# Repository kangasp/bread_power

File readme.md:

# Bread Board Power Module
Goal is to power a bread board.

## Reqs
* Use 18650 to power the board
* Ability to charge the battery with USB-C
* Form factor for bread board
* LEDs to indicate on / charging
* Fuse - resetable circuit protection

## Parts to use
* Boost:  C915088 Boost IC, TPS61022RWUR
* BMS:  C15220, BQ24073RGTR,    https://www.ti.com/lit/ds/symlink/bq24073.pdf?ts=1761246632036&ref_url=https%253A%252F%252Fwww.ti.com%252Fproduct%252FBQ24073%252Fpart-details%252FBQ24073RGTR%253Futm_source%253Dgoogle%2526utm_medium%253Dcpc%2526utm_campaign%253Dapp-null-null-app_opn_en-cpc-storeic-google-ww_en_pur%2526utm_content%253DDevice%2526ds_k%253DBQ24073RGTR%2526DCM%253Dyes%2526gclsrc%253Daw.ds%2526gad_source%253D1%2526gad_campaignid%253D8178941673%2526gbraid%253D0AAAAAC068F1OY5LTfCSqCOSRi7oG12xUk%2526gclid%253DCjwKCAjwpOfHBhAxEiwAm1SwEnpGtKfSzLroLLaXasqsRVhPzDe272zBBU-BZBLuSHX_bdEM7pz5ABoC5aUQAvD_BwE

* USB-C:  C3151650,     USB4125-GF-A
* Inductor (boost):  XAL7030-102MEC, C19191626, SMD,7.5x7.5mm
* Battery Holder: C2979183, MY-18650-01
* Thermistor:  C2892547, KNTC0603/10KF3950, 0603
* PGOOD LED: C34499, KT-0805W, white 0805
* CHG LED: C2297, KT-0805G, green 0805

* Resistors:
    * 5.1k: C25905      (0402) USB cc1 & cc2
    * 680:  C23228      (0603)  iset
    * 1.2k: C22765      (0603)  ilim
    * 1k:   C11702      (0402)  led cur limit
    * 100k: C25741      (0402)  voltage FB divider
    * 732k: C5159692    (0402)  voltage FB divider

Capacitors:
    * 22u:  C12891      (1206)  
    * 10u:  C15850      (0805)
    * 1u:   C28323      (0805)

Switch the battery symbol to be a one pin symbol and use 2.
Battery:BatteryClip_Keystone_54_D16-19mm

Plan to stradle the bread board.

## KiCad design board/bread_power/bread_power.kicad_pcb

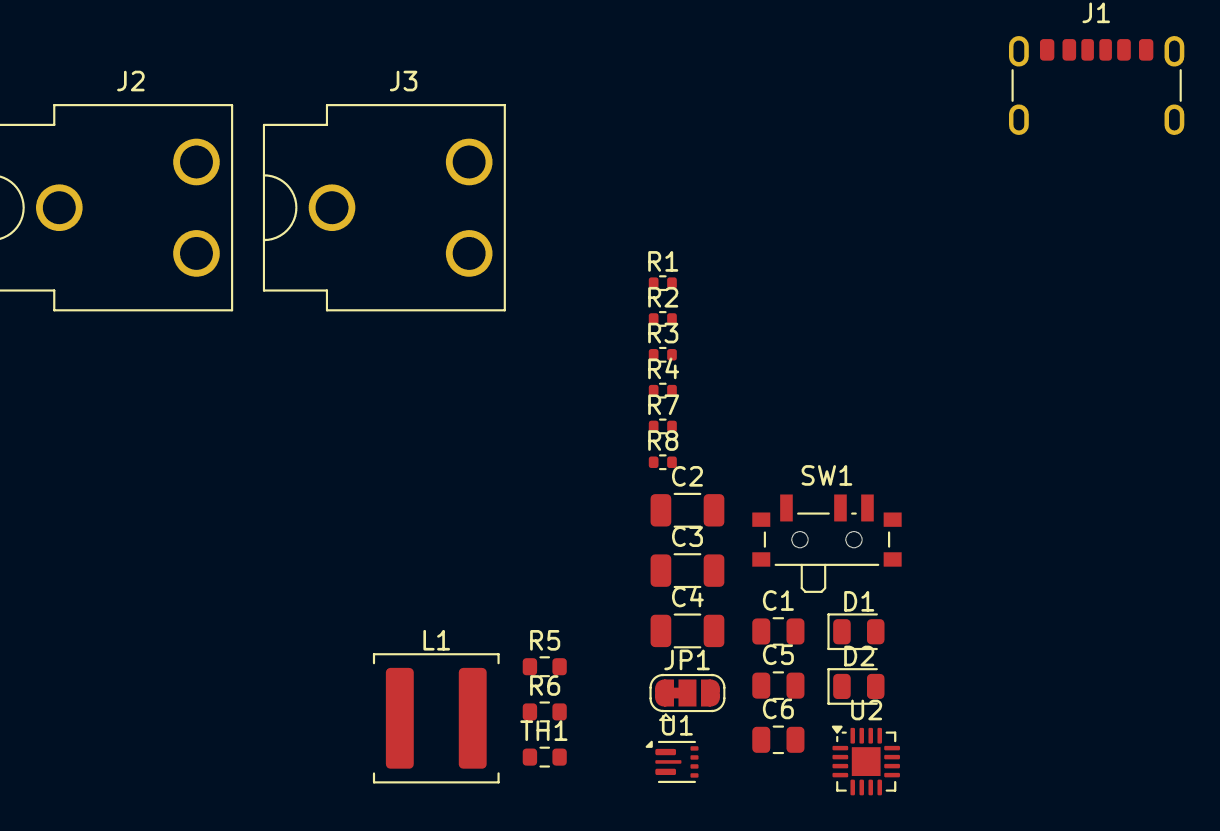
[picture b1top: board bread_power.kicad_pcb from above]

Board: 2 copper layers, 25 parts (0 on the bottom side), 18 nets, no tracks yet.

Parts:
C1: 10u; C_0805_2012Metric
C2, C3, C4: 22u; C_1206_3216Metric
C5, C6: 1u; C_0805_2012Metric
D1, D2: LED; LED_0805_2012Metric
J1: USB_C_Receptacle_PowerOnly_6P; USB_C_Receptacle_GCT_USB4125-xx-x-0190_6P_TopMnt_Horizontal
J2, J3: Conn_01x01_Pin; BatteryClip_Keystone_54_D16-19mm
JP1: SolderJumper_3_Bridged12; SolderJumper-3_P1.3mm_Bridged12_RoundedPad1.0x1.5mm
L1: 1u; L_Bourns_SRP6060FA
R1: 732k; R_0402_1005Metric
R2: 100k; R_0402_1005Metric
R3, R4: 5.1k; R_0402_1005Metric
R5: 680; R_0603_1608Metric
R6: 1.2k; R_0603_1608Metric
R7, R8: 1k; R_0402_1005Metric
SW1: SW_SPDT; SW_SPDT_PCM12
TH1: Thermistor_NTC; R_0603_1608Metric
U1: TPS61022; Texas_RWU0007A_VQFN-7_2x2mm_P0.5mm
U2: BQ24073RGT; VQFN-16-1EP_3x3mm_P0.5mm_EP1.6x1.6mm

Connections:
BATTV: C1.1, JP1.3 (B), L1.1, R7.1, R8.1, SW1.3 (C), U1.7 (VIN), U2.5 (EN2), U2.10 (OUT), U2.11 (OUT)
Batt+: C6.1, J2.1, U2.2 (BAT), U2.3 (BAT)
GND: C1.2, C2.2, C3.2, C4.2, C5.2, C6.2, J1.A12 (GND), J1.B12 (GND), J1.S1 (SHIELD), J3.1, JP1.1 (A), R2.2, R3.2, R4.2, R5.2, R6.2, SW1.1 (A), TH1.2, U1.1 (GND), U2.4 (~CE), U2.6 (EN1), U2.8 (VSS), U2.14 (TMR), U2.15 (TD), U2.17 (VSS)
unnamed: D1.2 (A), R7.2
unnamed: D1.1 (K), U2.7 (~PGOOD)
unnamed: D2.2 (A), R8.2
unnamed: D2.1 (K), U2.9 (~CHG)
unnamed: J1.A5 (CC1), R4.1
unnamed: J1.B5 (CC2), R3.1
unnamed: JP1.2 (C), U1.6 (MODE)
unnamed: SW1.2 (B), U1.5 (EN)
unnamed: R1.2, R2.1, U1.4 (FB)
unnamed: L1.2, U1.2 (SW)
unnamed: R6.1, U2.12 (ILIM)
unnamed: C5.1, J1.A9 (VBUS), J1.B9 (VBUS), U2.13 (IN)
unnamed: R5.1, U2.16 (ISET)
unnamed: TH1.1, U2.1 (TS)
VOUT: C2.1, C3.1, C4.1, R1.1, U1.3 (VOUT)

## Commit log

2025-09-19 Initial goals for project.
2025-10-02 Add board
    Add Board
2025-10-02 Adding some layout for the BMS circuit.
2025-10-09 Chose thermistor, battery holder, LEDs, etc.
2025-11-11 Updates for part annotations.
